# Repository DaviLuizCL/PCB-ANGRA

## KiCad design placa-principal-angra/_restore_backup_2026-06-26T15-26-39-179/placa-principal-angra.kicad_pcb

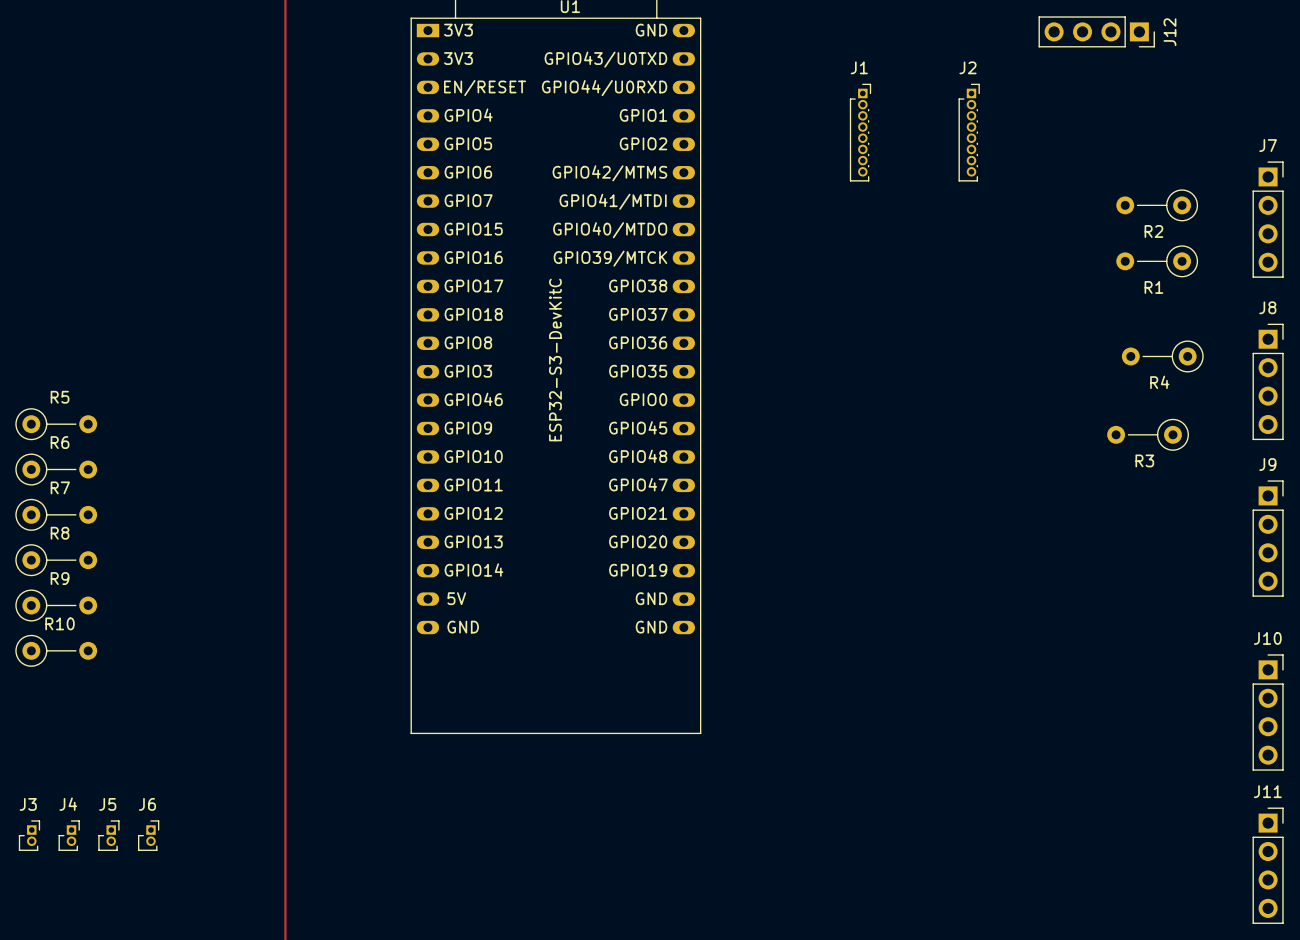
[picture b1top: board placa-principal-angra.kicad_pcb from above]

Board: 2 copper layers, 23 parts (0 on the bottom side), 32 nets, no tracks yet.

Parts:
J1: ENTRADA-PH; PinSocket_1x08_P1.00mm_Vertical
J2: SAÍDA PH; PinSocket_1x08_P1.00mm_Vertical
J3, J4, J5, J6: PinSocket_1x02_P1.00mm_Vertical
J7: SONAR-1; PinSocket_1x04_P2.54mm_Vertical
J8: SONAR-2; PinSocket_1x04_P2.54mm_Vertical
J9: SONAR-3; PinSocket_1x04_P2.54mm_Vertical
J10: SONAR-4; PinSocket_1x04_P2.54mm_Vertical
J11: SONAR-5; PinSocket_1x04_P2.54mm_Vertical
J12: MPU; PinSocket_1x04_P2.54mm_Vertical
R1, R3, R5, R7, R9: 1K; R_Axial_DIN0207_L6.3mm_D2.5mm_P5.08mm_Vertical
R2, R4, R6, R8, R10: 2K; R_Axial_DIN0207_L6.3mm_D2.5mm_P5.08mm_Vertical
U1: ESP32-S3-DevKitC

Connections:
/3V3: J2.7, J12.4, U1.1 (3V3), U1.2 (3V3)
/5V: J7.4, J8.4, J9.4, J10.4, J11.4, U1.21 (5V)
/A01: J2.5, J5.1, J6.2
/A02: J2.4, J5.2, J6.1
/B01: J2.2, J3.1, J4.2
/B02: J2.3, J3.2, J4.1
/ECHO1: R1.2, R2.2, U1.17 (GPIO11/ADC2_CH0)
/ECHO2: R3.2, R4.2, U1.19 (GPIO13/ADC2_CH2)
/ECHO3: R5.2, R6.2, U1.27 (GPIO21)
/ECHO4: R7.2, R8.2, U1.33 (GPIO36)
/ECHO5: R9.2, R10.2, U1.35 (GPIO38)
/GND: J1.8, J2.1, J2.6, J7.1, J8.1, J9.1, J10.1, J11.1, J12.3, R2.1, R4.1, R6.1, R8.1, R10.1
/GPIO4: J1.4, U1.4 (GPIO4/ADC1_CH3)
/GPIO5: J1.1, U1.5 (GPIO5/ADC1_CH4)
/GPIO6: J1.3, U1.6 (GPIO6/ADC1_CH5)
/GPIO7: J1.2, U1.7 (GPIO7/ADC1_CH6)
/GPIO15: J1.7, U1.8 (GPIO15/ADC2_CH4/32K_P)
/GPIO16: J1.5, U1.9 (GPIO16/ADC2_CH5/32K_N)
/GPIO17: J1.6, U1.10 (GPIO17/ADC2_CH6)
/SCL: J12.1, U1.15 (GPIO9/ADC1_CH8)
/SDA: J12.2, U1.12 (GPIO8/ADC1_CH7)
/TRIG1: J7.3, U1.16 (GPIO10/ADC1_CH9)
/TRIG2: J8.3, U1.18 (GPIO12/ADC2_CH1)
/TRIG3: J9.3, U1.11 (GPIO18/ADC2_CH7)
/TRIG4: J10.3, U1.32 (GPIO35)
/TRIG5: J11.3, U1.34 (GPIO37)
unnamed: J7.2, R1.1
unnamed: J8.2, R3.1
unnamed: J9.2, R5.1
unnamed: J10.2, R7.1
unnamed: J11.2, R9.1
unnamed: U1.22 (GND), U1.23 (GND), U1.24 (GND), U1.44 (GND)

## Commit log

2026-06-26 feat: Trazendo os componentes pra placa
2026-06-26 feat: salvei
2026-06-26 feat: Ajustando o roteamento
2026-06-26 feat
